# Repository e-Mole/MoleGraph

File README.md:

# MoleGraph: Open-Source School Probeware & STEM Toolkit

**MoleGraph** is an open-source, low-cost school probeware system designed for **hands-on STEM education**. Unlike commercial "black box" solutions, it follows a **"white box" approach**, allowing students and teachers to understand the inner workings of measurement technology, electronics, and sensor calibration. Multi-language user interface: English, Czech, German, French, Spanish, Polish, Portuguese, Italian, and Hungarian.

By engaging in the **DIY (Do-It-Yourself) assembly process**—which includes soldering, 3D printing, and component sourcing—users develop deep technological literacy and critical thinking skills.

---

## 🛠️ Online Tools
We provide a set of interactive online tools that run directly and securely in your web browser. Available in both **English and Czech**:

👉 **[MoleGraph Online Tools Hub](https://e-mole.github.io/MoleGraph/)**
- **Chemistry Laboratory:** An interactive environment for spectrophotometric analysis (Beer-Lambert law, transmittance, absorbance, and RGBC channel comparison) designed for data measured by the TCS34725 sensor.
- **Color Laboratory:** An interactive environment for color analysis and simulation (HSV, RGB, CMYK, CIELAB) designed for data measured by the TCS34725 sensor.
- **Sensor Editor (Teachers):** A simplified tool to hide unused sensors or modify text labels for younger students.
- **JSON Config Editor (Developers):** An advanced editor for customizing the `sensors.json` file when adding new sensors to custom firmware.

---

## 🏗️ Hardware Architecture & Modular Construction
The system is built on the **Arduino platform**, specifically utilizing the **Arduino NANO** (ATmega328) microcontroller and an **HC-05 Bluetooth module** for wireless connectivity.

- **[MoleGraph Shield U01](https://www.e-mole.cz/diy/molegraph-shield):** A custom-designed expansion PCB that features **standard RJ12 connectors** for robust and reliable sensor connectivity, replacing unstable breadboard wires.

- **Sensor Catalog:** A complete overview of currently supported sensors, including their descriptions and basic specifications, is available in the **[MoleGraph Sensor Catalog](https://www.e-mole.cz/diy/molegraph/sensors)**.

- **Mechanical Compatibility:** All components are housed in **[3D-printed cases (MoleBoxes)](https://www.e-mole.cz/diy/molebox)** that are fully compatible with the **[m-BITBEAM](https://www.e-mole.cz/diy/m-bitbeam) and BITBEAM** open-source construction sets.

- **LEGO Integration:** These cases share dimensions and hole spacing with **LEGO Technic**, allowing sensors to be integrated directly into robotic and mechanical models.

---

## ⚙️ Hardware Parameters (MoleGraph Unit U01)

| Feature | Specification |
| :--- | :--- |
| **Sensor Ports** | 4× **RJ12 ports**, each equipped with a **programmable function button** (e.g., for sensor resetting or triggering). |
| **Actuators** | Ports 2 and 3 natively support the connection of **servo motors**, enabling automation and robotics tasks. |
| **Status Indicators** | Onboard LEDs for **battery status**, active **Bluetooth/USB** connection, and ongoing **data recording**. |
| **Power Supply** | Flexible power via a **9V battery (6LR61)** or a **USB connection**. |
| **Connectivity** | Dual communication modes supporting **USB cable** (serial-to-USB) and wireless **Bluetooth SPP**. |
| **Analog Sensors** | 0–5V range using the integrated **10-bit ADC**. |
| **Digital Sensors** | Supports protocols like **I²C, OneWire, and PWM**. |
| **Extensibility** | Currently **`MoleGraphAuto` library** supports **30+ sensor types**. Includes "universal cables" and breadboard modules for connecting any custom 0–5V sensor. |

---

## 🖥️ Software & Data Analysis
The system includes a powerful cross-platform application and a specialized firmware layer.

| Feature | Details |
| :--- | :--- |
| **Platforms** | Native support for **MS Windows, Linux, macOS, and Android**. |
| **Measurement** | Manages up to **8 independent channels** simultaneously. |
| **Sampling** | Continuous sampling (up to **~1 kHz** for one analog) or **on-demand sampling** triggered manually. |
| **Visualization** | Real-time **graphs** (with multiple independent Y-axes) and **digital panels** for numerical display. |
| **Analytics** | Graph reading tools and basic **statistics** (min, max, mean, median, standard deviation). |
| **Calibration** | Built-in calibration/correction dialog using formula, e.g. $y = bx + a$. |
| **Education** | Teachers can create experiment templates ("Save/Open without values"), allowing students to start measuring immediately. |
| **Export** | Export results to **CSV** (tabular data) and graphs to **PNG** images. |

---

## 💻 Programming & Robotics Integration
MoleGraph facilitates a smooth transition from basic measurements (**`MoleGraphAuto` library**) to advanced coding and engineering.

### 1. Visual Programming
Beginners can use **[Blockly@rduino](https://github.com/e-Mole/Arduino)** with a custom MoleGraph extension (and **`MoleGraphManual` library**) to build programs graphically, automatically generating standard Arduino (C++) code.

👉 **[Launch Blockly@rduino in Browser](https://e-mole.github.io/Arduino)** *(Defaults to Arduino Nano, available in EN/CZ)*

### 2. Advanced Coding
The **`MoleGraphManual` library** allows for custom firmware development in the Arduino IDE, enabling simultaneous data transmission and control of external actuators.

### 3. Robotics
Highly compatible with projects like the [**"Fretka" robot**](https://www.e-mole.cz/clanek/bezdratova-komunikace-pro-fretku), which can transmit real-time sensor data wirelessly to the MoleGraph application.

---

## 🎓 Academic Background
This project is based on research outcomes from a doctoral dissertation thesis at Charles University Prague. It explores the implementation of open-source probeware systems in STEM education.
- **Dissertation Thesis (CUNI Repository):** [A Tool for STEM Education: Open-Source and School Probeware Systems](https://dspace.cuni.cz/handle/20.500.11956/211517)

- **Journal Article:** [MoleGraph: A Tool for Developing Scientific and Digital Skills in Schools](https://doi.org/10.54779/chl20250208)

- **Journal Article:** [Molegraph: DIY Sensors for School Experiments and Their Comparison with Commercial Options](https://doi.org/10.54779/chl20250357)

- **Conference Paper:** [DIY or Commercial Sensors for STEM Teaching?](https://doi.org/10.1088/1742-6596/3037/1/012007)

---

## Different Arduino and MoleGraph setups

## MoleGraph shield

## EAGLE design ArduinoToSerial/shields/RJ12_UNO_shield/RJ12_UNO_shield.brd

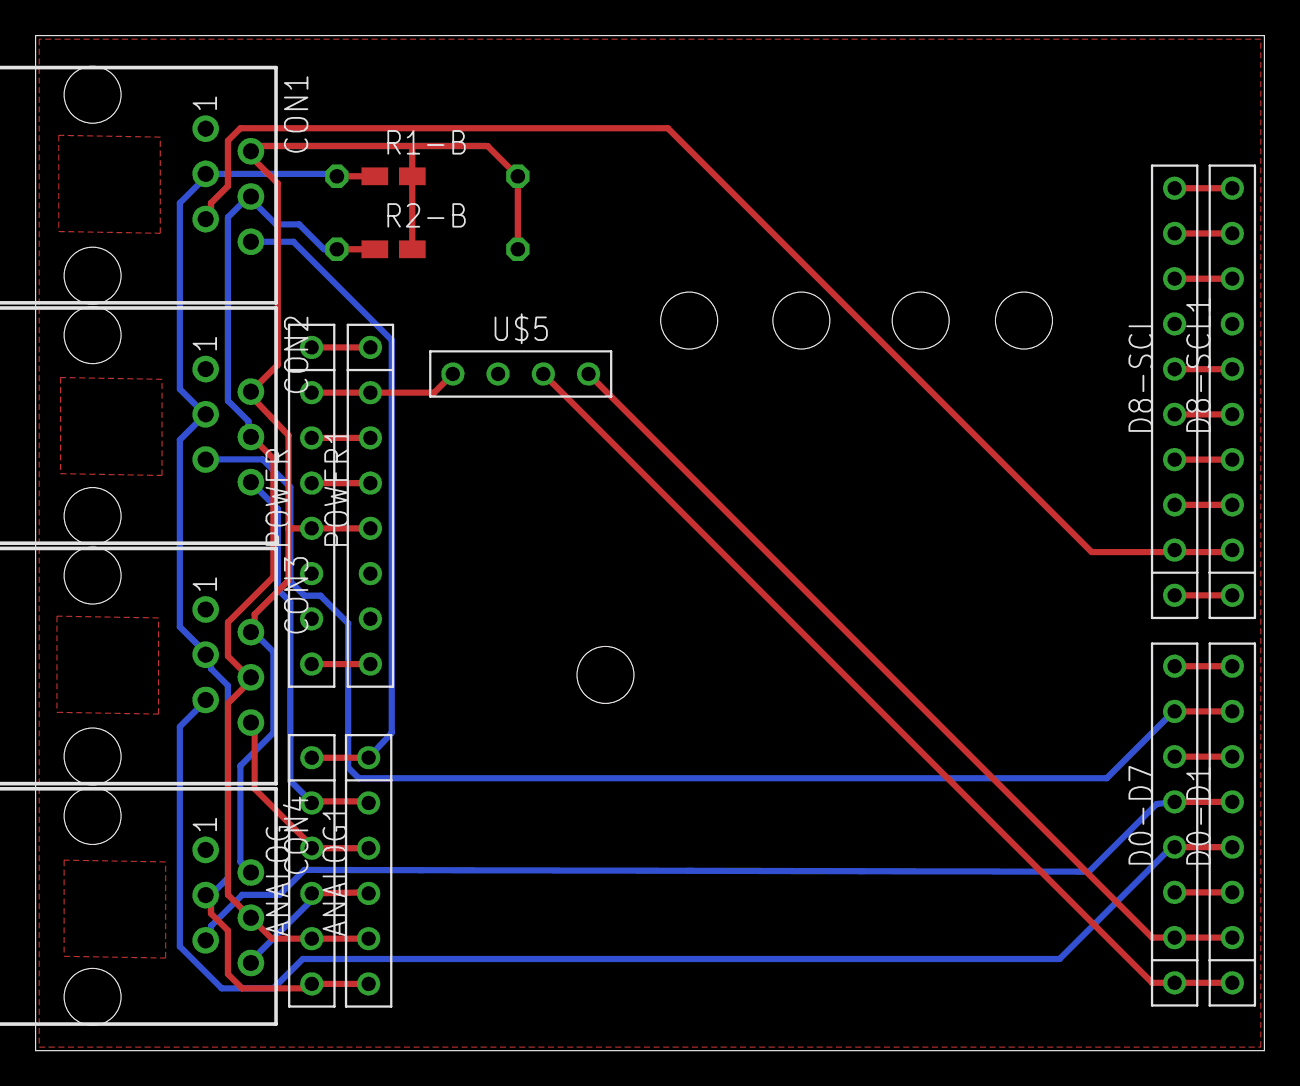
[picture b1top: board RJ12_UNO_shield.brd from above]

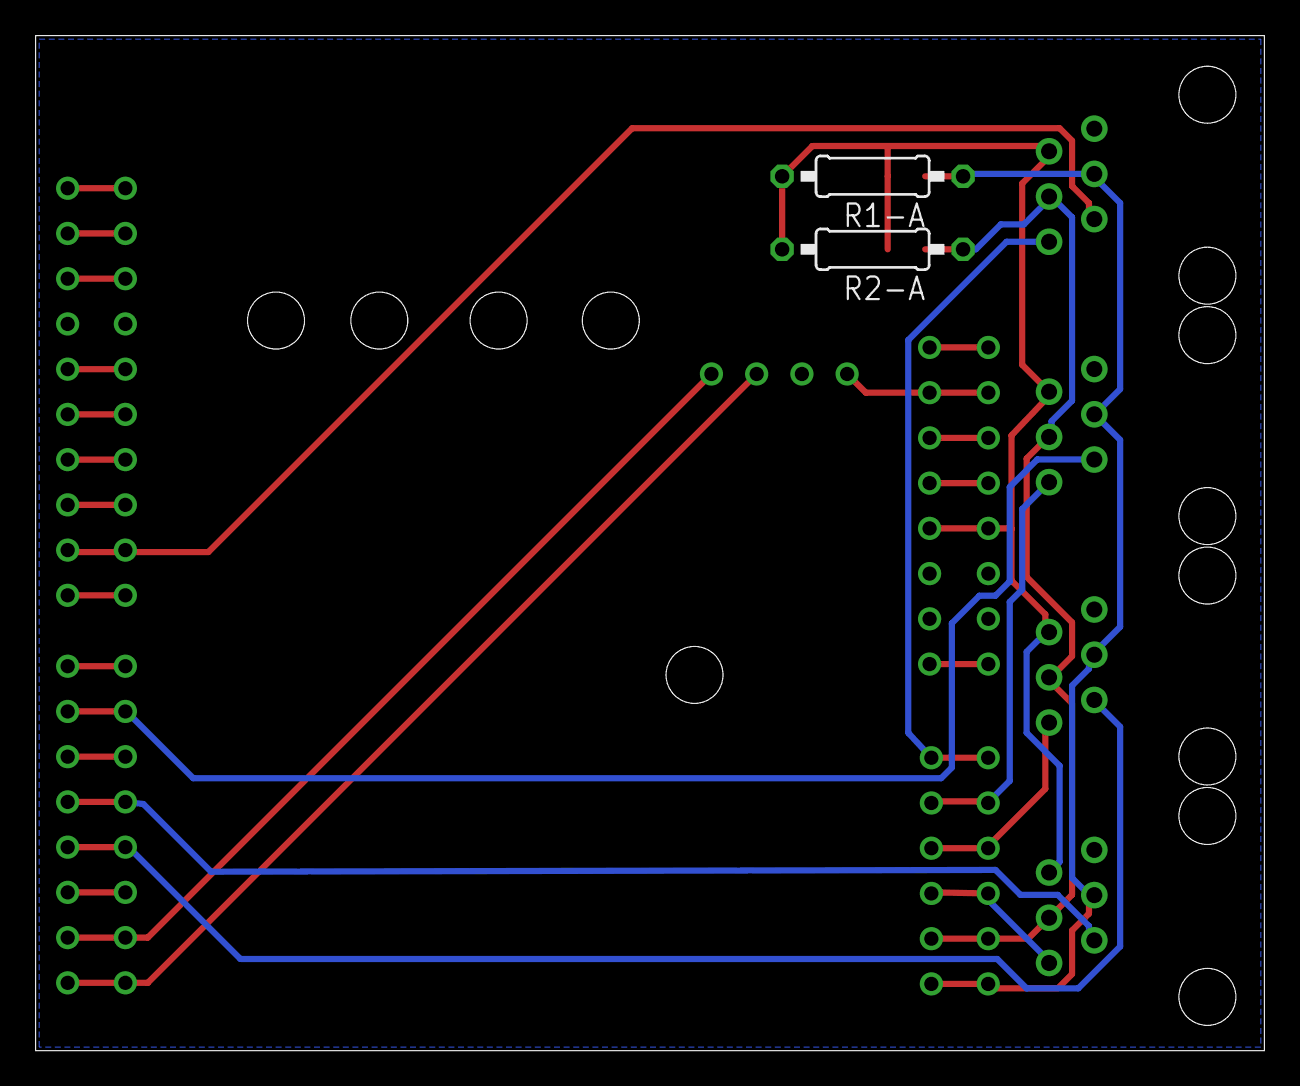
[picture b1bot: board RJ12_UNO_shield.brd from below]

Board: 2 copper layers, 69.0 x 57.0 mm, 17 parts (2 on the bottom side), 30 nets.

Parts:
ANALOG, ANALOG1: ANALOG
CON1, CON2, CON3, CON4: RJ12
D0-D1, D0-D7: DIGITAL0-7
D8-SCL, D8-SCL1: DIGITAL8-SCL
POWER, POWER1: POWER
R1-A, R2-A: 0207/10
R1-B, R2-B: R0805W
U$5: BLUETOOTH

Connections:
GND: CON1.1, CON2.1, CON3.1, CON4.1, D8-SCL.GND, D8-SCL1.GND, POWER.GBD(2), POWER.GND(1), POWER1.GBD(2), POWER1.GND(1), U$5.GND
unnamed: ANALOG.A5, ANALOG1.A5, CON1.3, CON2.3, CON3.3, CON4.3, R1-A.1, R1-B.1
unnamed: ANALOG.A4, ANALOG1.A4, CON1.4, CON2.4, CON3.4, CON4.4, R2-A.1, R2-B.1
unnamed: CON2.5, D0-D1.D6, D0-D7.D6
unnamed: ANALOG.A2, ANALOG1.A2, CON3.6
unnamed: ANALOG.A1, ANALOG1.A1, CON2.6
unnamed: ANALOG.A0, ANALOG1.A0, CON1.6
unnamed: POWER.NC, POWER1.NC
unnamed: POWER.RES, POWER1.RES
unnamed: POWER.3V3, POWER1.3V3
unnamed: POWER.VIN, POWER1.VIN
unnamed: D8-SCL.SCL, D8-SCL1.SCL
unnamed: POWER.5V(1), POWER1.5V(1), U$5.5V
unnamed: D8-SCL.SDA, D8-SCL1.SDA
unnamed: D0-D1.D0, D0-D7.D0, U$5.TX
unnamed: D0-D1.D1, D0-D7.D1, U$5.RX
unnamed: D8-SCL.AREF, D8-SCL1.AREF
unnamed: CON4.5, D0-D1.D4, D0-D7.D4
unnamed: D8-SCL.D13, D8-SCL1.D13
unnamed: CON3.5, D0-D1.D3, D0-D7.D3
unnamed: D8-SCL.D12, D8-SCL1.D12
unnamed: D8-SCL.D11, D8-SCL1.D11
unnamed: CON1.5, D8-SCL.D9, D8-SCL1.D9
unnamed: D8-SCL.D10, D8-SCL1.D10
unnamed: D8-SCL.D8, D8-SCL1.D8
unnamed: D0-D1.D7, D0-D7.D7
unnamed: D0-D1.D2, D0-D7.D2
unnamed: ANALOG.A3, ANALOG1.A3, CON4.6
unnamed: CON1.2, CON2.2, CON3.2, CON4.2, POWER.5V(2), POWER1.5V(2), R1-A.2, R1-B.2, R2-A.2, R2-B.2
unnamed: D0-D1.D5, D0-D7.D5

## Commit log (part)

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2018-02-13 bugfix: added horizontal channel mapping for new measurement
2018-02-13 bugfix: pen style should not be forced when is changed
2018-02-16 Measurement removing together with its channel ghosts
2018-02-17 ghost channel renamed to virtual channel
2018-02-19 bugfix: ghost channel features was not changed when was changed original measurement
2018-02-24 mew value set is tracked in for ghost too
2018-02-24 removed file commited by mistake
2018-02-25 ghost channel storing
2018-02-25 it must be moved or redesign. currently are q_properties in widget
2018-03-02 addGhostChannelActivated is commented out on next branch yet
2018-03-04 Sensors without storing to .mogr file.
2018-03-05 fallback solution not pressent sensor file
2018-03-08 cleaning
2018-03-08 fix of bug. it should be able to store startDateTime again. rest of SampleChannel meta properties have to be moved and are not fixed yet
2018-03-08 Sensor JSON file update
2018-03-08 Added new MoleGraphAuto firmware.
2018-03-08 New protocol version - ATG_5
2018-03-08 hotfix: now is accepted firmware version 4 and 5 - temporary solution!
2018-03-09 Change Voltage ID in ad.cpp
2018-03-09 Removed bug in AD "generic sensor" code
2018-03-13 Fix quantities order based on position in array.
2018-03-13 Some sensor modules code modifications for reading analog + digital(as trigger) and adding dirty autozero for pressure and force sensors.
2018-03-13 Update JSON sensors config file.
2018-03-15 bugfix: added check for legacy firmware. unsupported message is not send any more
2018-03-15 Fix sensors: AD, DHT11, sonar SR-04.
2018-03-16 bugfix: in the beggning of the method is replot disabled, on the end must be anabled again
2018-03-16 bugfix: removed quick hack
2018-03-17 bugfix: following each measured value-set slows down drawing until it was stopped I hope it is finally done
2018-03-18 fix of channel data storing
2018-03-18 storing channel sensor properties to .mogr file
2018-03-18 bugfix: ghost channel functionality has been deactivated on next branch. now it is available again
2018-03-19 Created SampleChannelProperties class and moved there all related enums and methods
2018-03-23 added shape None + when is set shape None and No_Line graph doesn't use it for scaling
2018-03-24 bugfix: overwriting properties when ChannelSettings is open
2018-03-24 removed unused methods + Horizontal axes is updated when ghost is added/removed
2018-03-24 not finished. just to be stored
2018-03-24 bugfix: axes with channels without data should be diplayed. I dont want to display axes without channels
2018-03-24 bugfix: wrong shortcut index for sample channel
2018-03-25 bugfix: channelEditin signals are registered only when ghost channel is creating
2018-03-25 bugfix: cloned ghost cannels had properties from wrong channel
2018-03-25 sensors are in resources now.
2018-03-26 - Fix bug in classical MoleGraph FW - Added MoleGraph shield (for Arduino NANO)
2018-03-29 ChannelProperties
2018-04-02 add comment for shapeIndex
2018-04-03 fixed wrong retyping
2018-04-06 fixes for ChannelProxy refactoring
2018-04-06 bugfix: hard comparsion of floats is not really reliable - now it is used qFuzzyCompare instead.
2018-04-06 refactoring: IsValueNA and GetLastValidValue has been moved from ChannelBase to ChannelProxyBase
2018-04-06 refactoring: logic from SampleChannel::GetValue has been moved to SampleChannelProxy
2018-04-09 refactoring: ChannelProxyBase contains features of ChannelWidget now
2018-04-11 added horizontal channel to ghost settings
2018-04-14 Created ChannelPropertoies -> now it is possible to switch to sample ghost but it is still not possible to confirm
2018-04-17 sample channel ghost - still some open issues
2018-04-20 sample channel can be a ghost
2018-04-23 fixes for ghost channels - now is horizontal channel for ghost based on main horizontal channel index
2018-04-24 fix of bug: serialization/deserialization of time features fix of bug: re-sorting loaded measurements where samples are not on horiontal axis
2018-04-26 bugfix: switching to channel ghost from a measurement which is not present
2018-04-28 serialization of channel graphics variables are now placed in proxy to be possible apply all of them
2018-04-28 just moved body of method to .c
2018-04-28 RealTime text must be taken from proxy value to be valid
2018-04-29 Untracked SampleChannelPropertiesChanged when are filled properties.
2018-04-29 bugfix: ghost was not deserialized properly
2018-05-01 fixed issue when file is not readable and set to open at startup
2018-05-03 uncomment git version getting - comminted by mistake
2018-05-16 Added MH-Z16 CO2 sensor.
2018-05-17 bugfix: addNewValueSet was added for main measurement for all channels
2018-05-17 bugfix: for setOriginalValue
2018-05-27 removed offset combo, adjustment multiplier combo
2019-08-19 adjusted sized of check boxes and radio boxes to be based on dpi (to be clickable on android) adjusted text font size it seems that label font is not taken from windows settings
2019-08-20 removed workaround - radio button size is set explicitly
2019-11-26 Sensors.json update
2019-11-26 Added pH sensor module
2019-11-27 Added luxmeter based on BH1750.
2019-11-28 Added LSM303 Accelerometer + Magnetometer.
2019-12-20 bugfix: measurement may contain channels unassigned to a sensor. more channels can watch the same sensor
2019-12-20 removed cleaning values that is probably useless moreover prevents to use one sensor value for more channels.
2019-12-21 Translation - added new CS translation Added missing include (#include <QVector> in HwConnector.h)
2019-12-21 for sure for bluetooth on windows. sometimes was not read everything.
2019-12-22 bugfix: when was changed measurement only channel proxy has not been changed properly.
2019-12-23 Added UNITS to json confic file.
2019-12-29 JSON extension with the possibility of correction (offset, offset+slope)
2020-01-01 bugfix: serial port should be available for unix too.
2020-01-03 Update Timer sensor (description and quantities)
2020-01-04 bugfix: Bluetooth device used on Molegraph board have two services but only one can be connected as a serial port. the second one must be filtered out because on some smartphones is returned as the f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
2020-01-05 channel name is taken from appropriate sensor quantity
2020-02-09 value correction is serialized/deserialized to/from file
2020-02-14 value correction
2020-02-15 show all marks is possible to set for each channel
2020-02-18 value correction defined for a sensor component is filled when the sensor component is selected
2020-02-19 Added new string translations...
2020-02-24 Added translation strings for correction (En->Cs), disabled unfinished sensors in sensors.json
2020-02-26 bugfix: different count of channels was read than was written.
2020-03-05 storing information about reduced graph width to will will not be app stuck when opens file with a "slow" graph
2020-03-07 Added ECG AD8232 sensor New updated translations
2020-03-17 adjutments for android
2020-03-17 bugfix: # removed by mistake
2020-03-22 added sensors.json to installer package + fixed extension file text
2020-03-29 bugfixes: measurement was scaled wrongly when contains hidden ghost channel + ghost channel was not displayed on correct axes after loading from the file
2020-04-04 data are provided immediately when are ready after the measurement start
2020-04-04 bugfix: clear map when its items are deleted
2020-04-25 bugfix: original value was not displayed when user pressed original value button
2020-04-25 bugfix: when measurement with ghost is copied ghost was not placed on correct axes when these aces was not present in the ghost original measurement
2020-05-03 fixed name for ghost, fixed title for ghost and not ghost channels (shortcut number)
2020-08-03 removed unused code
2021-05-06 bugfix: ProcessData() is not part od the Sensor class any more. Must be used prcess() insted.
2021-05-06 Last working data sampling before Timer change.
2021-05-06 Martin: Timer change (v 0.3.2)
2021-05-07 Qcustomplot test: disable antialiasing
2021-11-27 bugfix: asm block should be volatile to be sure that will not be optimalized. refactoring: adjusted filling period (unify calculation for time and freq.)
2021-11-29 bugfix: every second sample was measurd in onDemand mode for DS1B820 - added check to dataReady for on demand samples bugfix: fixed wrong timestamp when internal time counter overflows bugfix: added 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
2023-03-05 Added "manual" FW for MoleGraph U01
2023-03-05 Extended Timer sensor - now with counter and counter reset with button on U01
2023-03-22 upgraded android settings (loaded templates) for jdk 11.017 sdk 9.0 ndk 21.3 android 31
2023-03-23 bugfix: adjusted message box text to be more precise.
2023-03-24 Change Timer in MoleGraph Arduino FW: - MoleGraphAuto FW now supports in Timer sensor independent Counter for port 1-4 - MoleGraphManual FW now supports running Servo motor on port 2 and 3
2023-03-24 Rename class MoleGraph to MolGraphManual in molegraphmanual.h and molegraphmanual.cpp files
2023-03-27 bugfix: seting value correction changed actual value only
2023-03-28 bugfix: new functions was not really restricted for legacy version of the arduino firmware
2023-03-29 Added two Servo example code
2023-04-01 correction points are taken from the sensor.jsom file
2023-04-02 bugfix: note button stayed disabled when the firs sensor was chosen.
2023-04-02 bugfix: from some reason in this version of qt (5.15.2) is inverted logic of keys - left key button moved plot to right and vice versa.
2023-04-03 android permissions authorisation moved to code to be aligned with Android >6
2023-04-07 Added MH-Z16 CO2 sensor (PWM measurement based on Timer sensor class).
2023-04-08 Moved startMeasurement and stopMeasurement to public
2024-01-21 Added Conductivity sensor (TDS/Salinity) with calibration data in sensors.json (µS/cm, ppm)
2024-01-26 - added forgotten strings to translate - updated translation - added the possibility of zeroing for the Generic sensor (the offset is set after pressing the F1-F4 button when the measurement is pause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
2024-01-28 - JSON translation correction
2024-02-26 bugfix: clean m_bluetooth in golobal_settings sen set it to null for the case it has been unchecked
2024-02-26 Added ClassRelations description in PNG and PDF
2024-03-17 bugfix: multiple times simulatously executed gitGetVersion.bat for the ancroid build
2024-03-18 Added MoleGraph SVG icon.
2026-01-13 Enhance README with detailed project info and links
    Expanded project description and added links for more information.
2026-01-16 Delete External/arduino-libs/HX711 directory
    - unused old dir
2026-01-16 Revise README to enhance project overview and details
    Expanded the README to provide detailed information about the MoleGraph system, including its hardware architecture, software features, and educational benefits.
2026-01-17 - Added a new section handling the port connection dialog for wireless BT on MS Windows. Instead of listing COM ports, BT devices are now listed under their actual name (e.g. MGA2-VIOLET). - New File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
2026-01-17 - Fix app version in .pro file (from Git Tag)
2026-01-17 - added MoleGraph code version number to MainWindow.cpp (window title)
2026-01-17 - fix bluetooth searching on win pc without BT or with BT module Off - fix sensor Info button in Chanell Settings dialog (now if is some sensor selected button is always enabled)
2026-01-21 [TEST:] Cloud settings dialog for future cloud data logging
2026-05-16 docs: add layout plan and parts list for PCB shield
    - Added PCB shield layout plan
    - Added Bill of Materials (parts list) for building the shield
    - Provided both documents in English (EN) and Czech (CS) versions
